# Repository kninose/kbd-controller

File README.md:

# kbd-controller

## Specifications
- Size: 300 x 100 mm
- KeySwitch: Cherry MX or Kailh Choc V2
- MicroController: Raspberry Pi Pico
- ScrewHole: M2

## KiCad Libraries
- Symbols: https://github.com/kninose/KiCad-Library/tree/main/Symbols
- Footprints: https://github.com/kninose/KiCad-Library/tree/main/Footprints

## License
This project is licensed under CC-BY-4.0. [LICENSE](LICENSE)

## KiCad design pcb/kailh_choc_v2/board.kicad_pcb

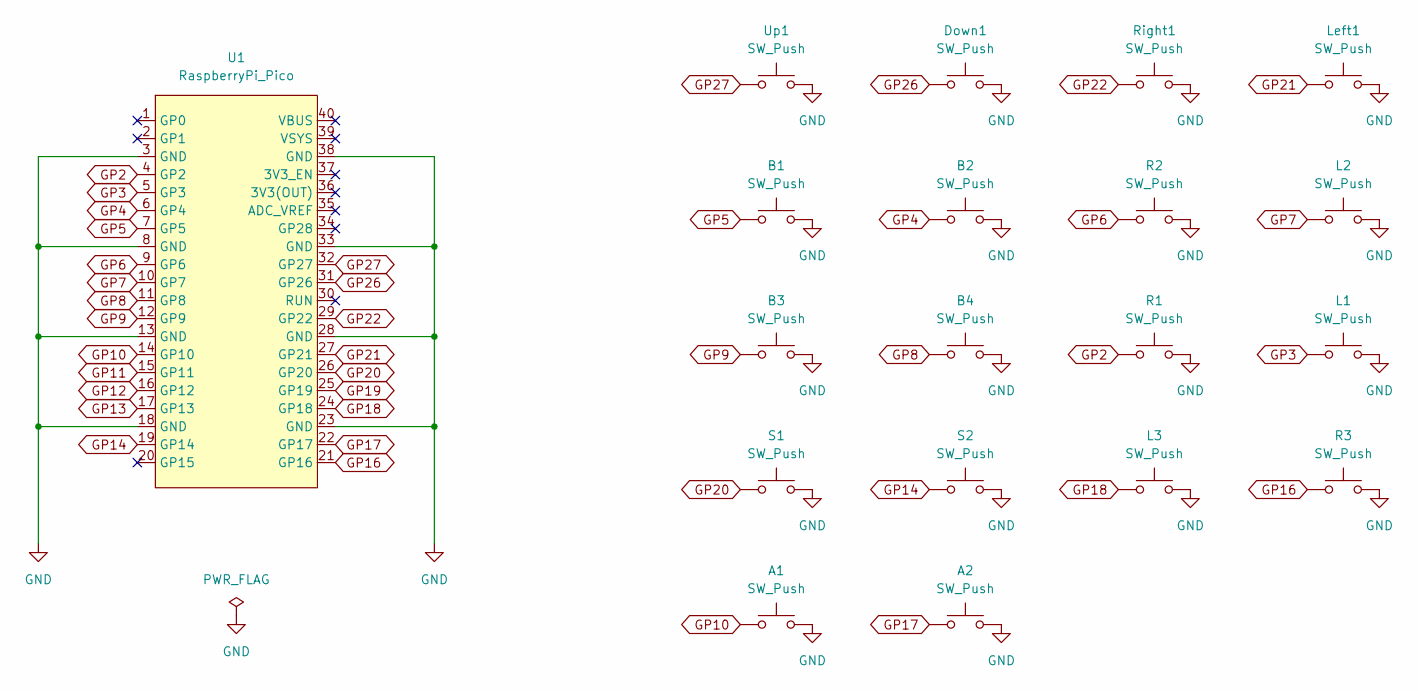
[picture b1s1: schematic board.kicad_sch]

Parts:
A1, A2: SW_Push; Kailh_Choc_V2_HotSwap_1U
B1, B2, B3, B4: SW_Push; Kailh_Choc_V2_HotSwap_1U
Down1: SW_Push; Kailh_Choc_V2_HotSwap_1U
L1, L2: SW_Push; Kailh_Choc_V2_HotSwap_1U
L3: SW_Push; Kailh_Choc_V2_HotSwap_2U
Left1: SW_Push; Kailh_Choc_V2_HotSwap_1U
R1, R2: SW_Push; Kailh_Choc_V2_HotSwap_1U
R3: SW_Push; Kailh_Choc_V2_HotSwap_2U
Right1: SW_Push; Kailh_Choc_V2_HotSwap_1U
S1: SW_Push; Kailh_Choc_V2_HotSwap_2.25U
S2: SW_Push; Kailh_Choc_V2_HotSwap_2.75U
U1: RaspberryPi_Pico
Up1: SW_Push; Kailh_Choc_V2_HotSwap_1U

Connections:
GND: A1.2, A2.2, B1.2, B2.2, B3.2, B4.2, Down1.2, L1.2, L2.2, L3.2, Left1.2, R1.2, R2.2, R3.2, Right1.2, S1.2, S2.2, U1.3 (GND), U1.8 (GND), U1.13 (GND), U1.18 (GND), U1.23 (GND), U1.28 (GND), U1.33 (GND), U1.38 (GND), Up1.2
GP2: R1.1, U1.4 (GP2)
GP3: L1.1, U1.5 (GP3)
GP4: B2.1, U1.6 (GP4)
GP5: B1.1, U1.7 (GP5)
GP6: R2.1, U1.9 (GP6)
GP7: L2.1, U1.10 (GP7)
GP8: B4.1, U1.11 (GP8)
GP9: B3.1, U1.12 (GP9)
GP10: A1.1, U1.14 (GP10)
GP11: U1.15 (GP11)
GP12: U1.16 (GP12)
GP13: U1.17 (GP13)
GP14: S2.1, U1.19 (GP14)
GP16: R3.1, U1.21 (GP16)
GP17: A2.1, U1.22 (GP17)
GP18: L3.1, U1.24 (GP18)
GP19: U1.25 (GP19)
GP20: S1.1, U1.26 (GP20)
GP21: Left1.1, U1.27 (GP21)
GP22: Right1.1, U1.29 (GP22)
GP26: Down1.1, U1.31 (GP26)
GP27: U1.32 (GP27), Up1.1

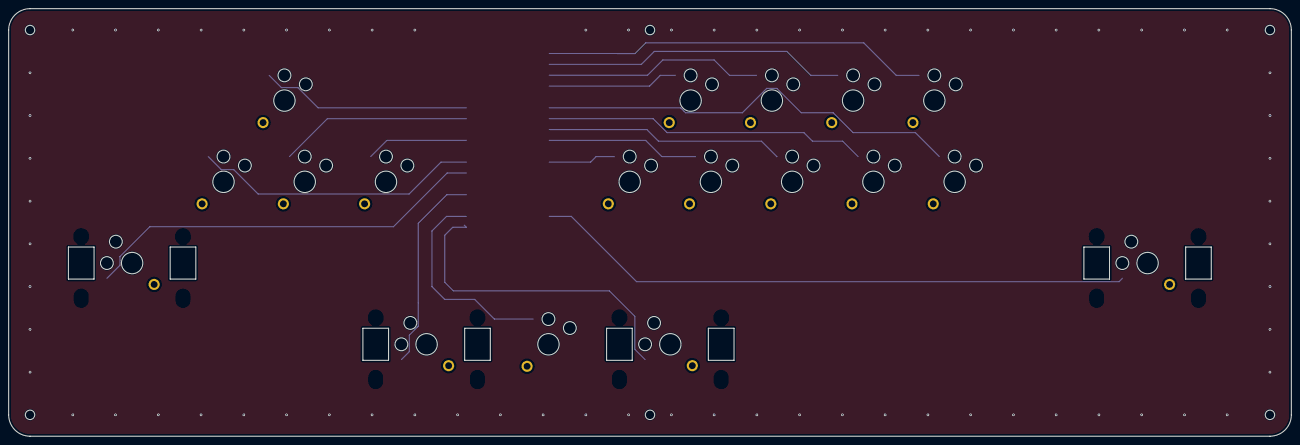
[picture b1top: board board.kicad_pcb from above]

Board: 2 copper layers, 300.0 x 100.0 mm, 19 parts (1 on the bottom side), 19 nets.
